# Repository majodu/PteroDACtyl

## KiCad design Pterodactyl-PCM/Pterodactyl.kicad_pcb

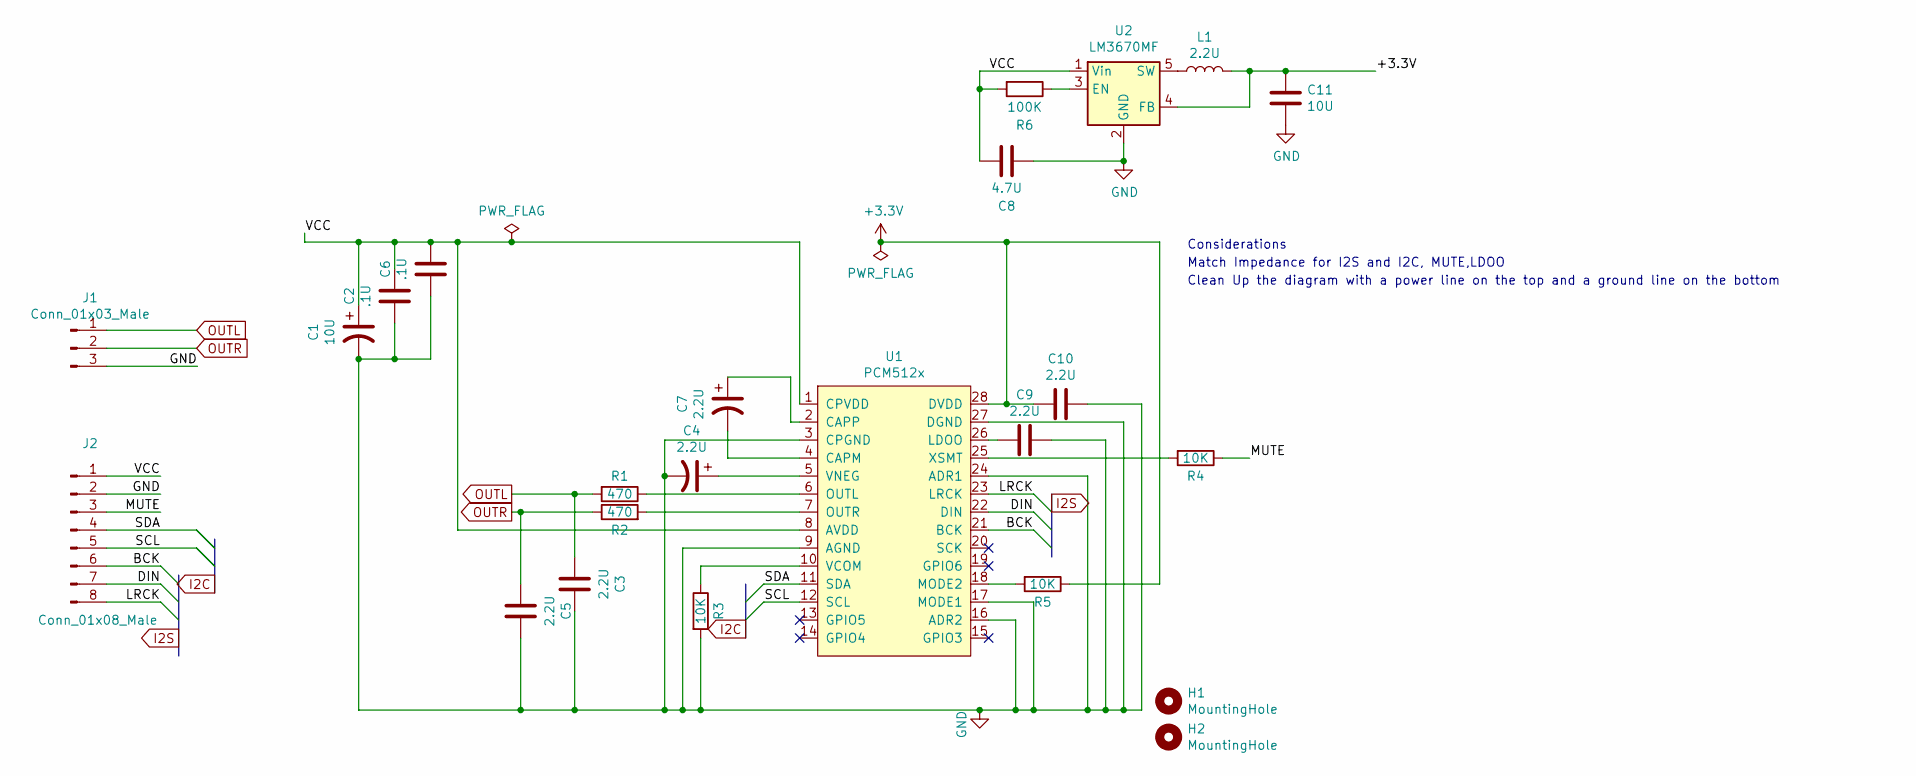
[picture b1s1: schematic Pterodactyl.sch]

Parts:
C1, C11: 10U; CP_Elec_4x4.5
C2, C6: .1U; C_0805_2012Metric_Pad1.18x1.45mm_HandSolder
C3, C5, C9, C10: 2.2U; C_0805_2012Metric_Pad1.18x1.45mm_HandSolder
C4, C7: 2.2U; CP_Elec_4x4.5
C8: 4.7U; CP_Elec_4x4.5
H1, H2: MountingHole; MountingHole_2.7mm_M2.5
J1: Conn_01x03_Male; PinHeader_1x03_P2.54mm_Vertical
J2: Conn_01x08_Male; PinHeader_1x08_P2.54mm_Vertical
L1: 2.2U; L_Wuerth_MAPI-3015
R1, R2: 470; R_0805_2012Metric_Pad1.20x1.40mm_HandSolder
R3, R4, R5: 10K; R_0805_2012Metric_Pad1.20x1.40mm_HandSolder
R6: 100K; R_0805_2012Metric_Pad1.20x1.40mm_HandSolder
U1: PCM512x; TSSOP-28-1EP_4.4x9.7mm_P0.65mm
U2: LM3670MF; TSOT-23-5

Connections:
+3V3: C10.2, R5.1, U1.28 (DVDD)
/+3.3V: C11.2, L1.2, U2.4 (FB)
/BCK: J2.6, U1.21 (BCK)
/DIN: J2.7, U1.22 (DIN)
/LRCK: J2.8, U1.23 (LRCK)
/MUTE: J2.3, R4.1
/SCL: J2.5, U1.12 (SCL)
/SDA: J2.4, U1.11 (SDA)
/VCC: C1.1, C2.1, C6.1, C8.1, J2.1, R6.2, U1.1 (CPVDD), U1.8 (AVDD), U2.1 (Vin)
GND: C1.2, C2.2, C3.2, C4.2, C5.2, C6.2, C8.2, C9.1, C10.1, C11.1, J1.3, J2.2, R3.2, U1.3 (CPGND), U1.9 (AGND), U1.16 (ADR2), U1.17 (MODE1), U1.24 (ADR1), U1.27 (DGND), U2.2 (GND)
unnamed: C4.1, U1.5 (VNEG)
unnamed: C7.1, U1.2 (CAPP)
unnamed: C7.2, U1.4 (CAPM)
unnamed: C9.2, U1.26 (LDOO)
unnamed: L1.1, U2.5 (SW)
unnamed: R1.1, U1.6 (OUTL)
unnamed: R2.2, U1.7 (OUTR)
unnamed: R3.1, U1.10 (VCOM)
unnamed: R4.2, U1.25 (XSMT)
unnamed: R5.2, U1.18 (MODE2)
unnamed: R6.1, U2.3 (EN)
OUTL: C3.1, J1.1, R1.2
OUTR: C5.1, J1.2, R2.1

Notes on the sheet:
Considerations
Match Impedance for I2S and I2C, MUTE,LDOO
Clean Up the diagram with a power line on the top and a ground line on the bottom

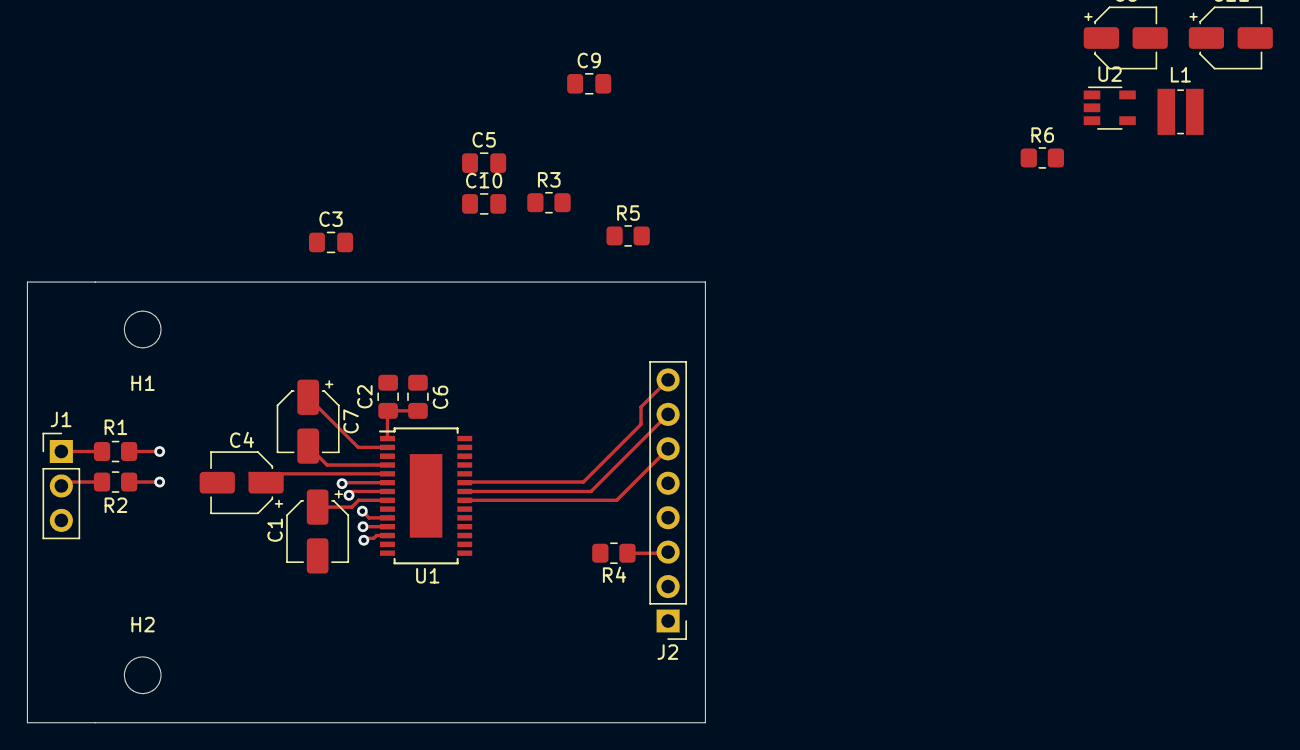
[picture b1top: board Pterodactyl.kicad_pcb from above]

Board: 2 copper layers, 50.0 x 32.5 mm, 24 parts (0 on the bottom side), 23 nets.

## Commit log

2021-04-17 audio dac chip Rev 1.0
2021-04-17 rename
2021-04-18 added DC regulator
